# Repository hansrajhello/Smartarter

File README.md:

# Smartarter
This is an Arduino based project to automate the operation of Irrigation pumps.

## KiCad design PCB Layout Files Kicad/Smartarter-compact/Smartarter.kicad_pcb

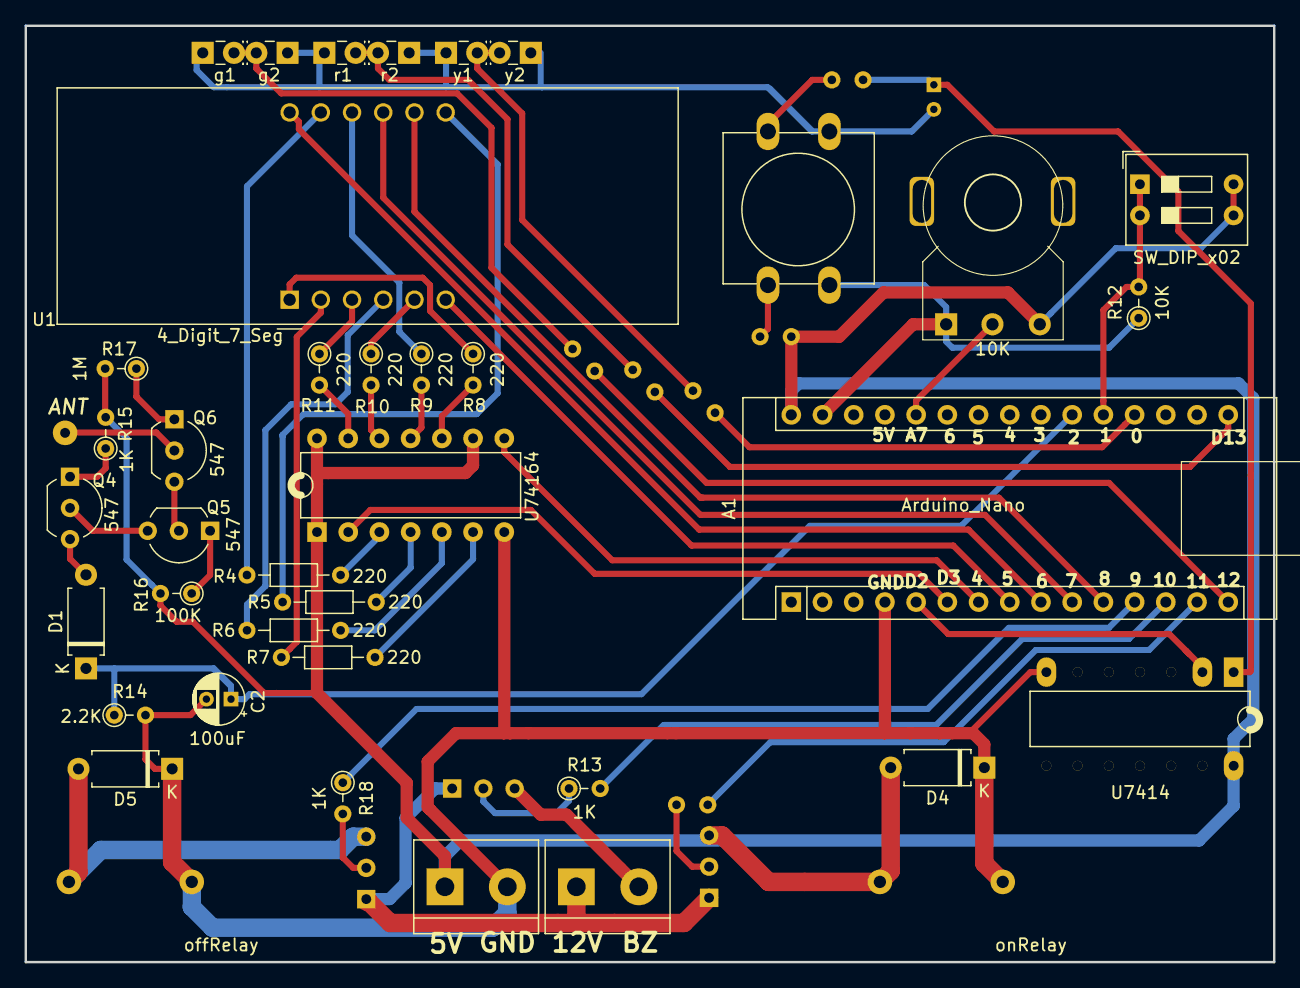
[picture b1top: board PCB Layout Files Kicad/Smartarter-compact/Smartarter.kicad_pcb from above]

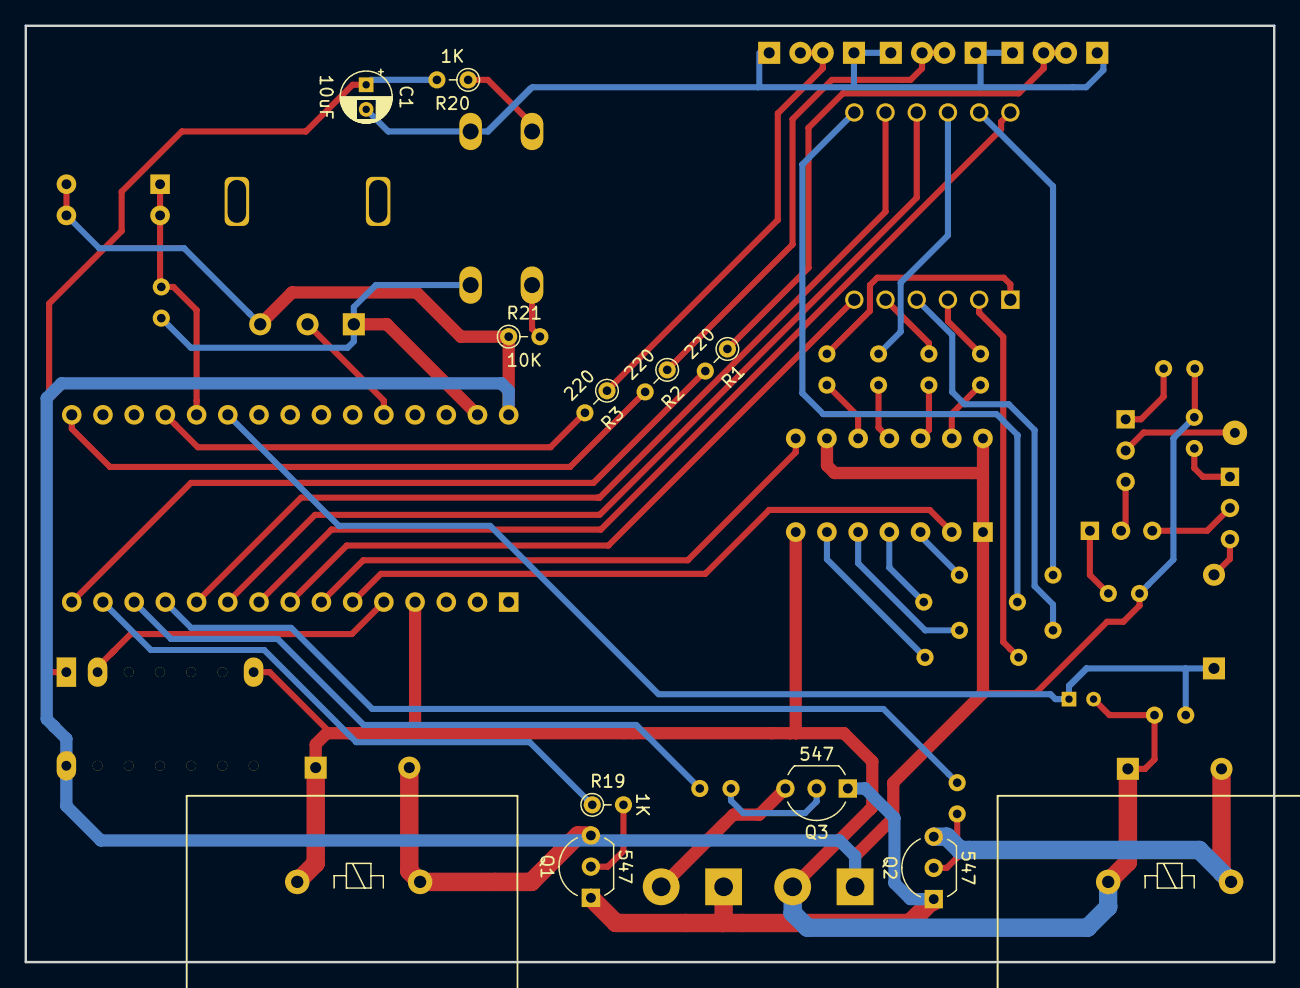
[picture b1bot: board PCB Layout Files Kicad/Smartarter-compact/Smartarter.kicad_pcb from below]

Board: 2 copper layers, 101.6 x 76.2 mm, 50 parts (12 on the bottom side), 53 nets.

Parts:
A1: Arduino_Nano
ANT1: ANT; SolderWirePad_1x01_Drill0.8mm
C1: 10uF; CP_Radial_D4.0mm_P2.00mm
C2: 100uF; CP_Radial_D4.0mm_P2.00mm
D1: D; D_A-405_P7.62mm_Horizontal
D4, D5: DIODE; D_A-405_P7.62mm_Horizontal
J1, J2: Screw_Terminal_01x02; TerminalBlock_bornier-2_P5.08mm
POT1: 10K; Potentiometer_Alpha_Round_P7.5
Q1, Q2, Q3, Q4, Q5, Q6: 547; TO-92_Inline_Wide
R1, R2, R3, R8, R9, R10, R11: 220; R_Axial_DIN0204_L3.6mm_D1.6mm_P2.54mm_Vertical
R4, R5, R6, R7: 220; R_Axial_DIN0204_L3.6mm_D1.6mm_P7.62mm_Horizontal
R12, R21: 10K; R_Axial_DIN0204_L3.6mm_D1.6mm_P2.54mm_Vertical
R13, R15, R18, R19, R20: 1K; R_Axial_DIN0204_L3.6mm_D1.6mm_P2.54mm_Vertical
R14: 2.2K; R_Axial_DIN0204_L3.6mm_D1.6mm_P2.54mm_Vertical
R16: 100K; R_Axial_DIN0204_L3.6mm_D1.6mm_P2.54mm_Vertical
R17: 1M; R_Axial_DIN0204_L3.6mm_D1.6mm_P2.54mm_Vertical
SW1: SW_Push; SW_PUSH-12mm
SW2: SW_DIP_x02; SW_DIP_SPSTx02_Slide_9.78x7.26mm_W7.62mm_P2.54mm
U1: 4_Digit_7_Seg; CA56-12EWA
U7414: 7414; DIP-14_W7.62mm_LongPads_Hansu
U74164: 74164; DIP-14_W7.62mm
g1, g2: onLED; LED_Rectangular_W3.9mm_H1.8mm
offRelay1: offRelay; Relay_SPDT_HUGE_32mm
onRelay1: onRelay; Relay_SPDT_HUGE_32mm
r1, r2: offLED; LED_Rectangular_W3.9mm_H1.8mm
y1, y2: otherLED; LED_Rectangular_W3.9mm_H1.8mm

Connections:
+5V: A1.30, J2.1, POT1.3, R15.2, R16.2, R17.2, R21.1, SW2.3, SW2.4, U7414.14, U74164.1, U74164.9, U74164.14
+12V: J1.1, Q1.1, Q2.1, Q3.1
/CLK: A1.7, U74164.8
/D1: A1.9, U1.12
/D2: A1.10, U1.9
/D3: A1.11, U1.8
/D4: A1.8, U1.6
/buzz: A1.13, R13.2
/bz: J1.2, Q3.3
/data: A1.6, U74164.2
/monitor: A1.21, C2.1, D1.1, R14.1
/offLed: A1.16, R2.2
/offRelay: A1.12, R18.1
/onLed: A1.15, R1.2
/onRelay: A1.14, R19.1
/otherLed: A1.19, R3.2
/pot: A1.26, POT1.2
/pushButton: A1.5, U7414.2
/slideSwitch: A1.20, R12.2, SW2.1, SW2.2
GND: A1.4, A1.29, C1.2, C2.2, D4.1, D5.1, J2.2, POT1.1, R12.1, R14.2, SW1.1, U7414.7, U74164.7, g1.1, g2.1, offRelay1.5, onRelay1.5, r1.1, r2.1, y1.1, y2.1
unnamed: ANT1.1, Q6.2
unnamed: C1.1, R20.2, U7414.1
unnamed: D1.2, Q4.3
unnamed: D4.2, Q1.3, onRelay1.1
unnamed: D5.2, Q2.3, offRelay1.1
unnamed: Q1.2, R19.2
unnamed: Q2.2, R18.2
unnamed: Q3.2, R13.1
unnamed: Q4.1, R15.1
unnamed: Q4.2, Q5.3
unnamed: Q5.1, R16.1
unnamed: Q5.2, Q6.3
unnamed: Q6.1, R17.1
unnamed: R1.1, g1.2, g2.2
unnamed: R2.1, r1.2, r2.2
unnamed: R3.1, y1.2, y2.2
unnamed: R4.1, U1.11
unnamed: R4.2, U74164.3
unnamed: R5.1, U1.7
unnamed: R5.2, U74164.4
unnamed: R6.1, U1.4
unnamed: R6.2, U74164.5
unnamed: R7.1, U1.2
unnamed: R7.2, U74164.6
unnamed: R8.1, U1.1
unnamed: R8.2, U74164.10
unnamed: R9.1, U1.10
unnamed: R9.2, U74164.11
unnamed: R10.1, U1.5
unnamed: R10.2, U74164.12
unnamed: R11.1, U1.3
unnamed: R11.2, U74164.13
unnamed: R20.1, R21.2, SW1.2

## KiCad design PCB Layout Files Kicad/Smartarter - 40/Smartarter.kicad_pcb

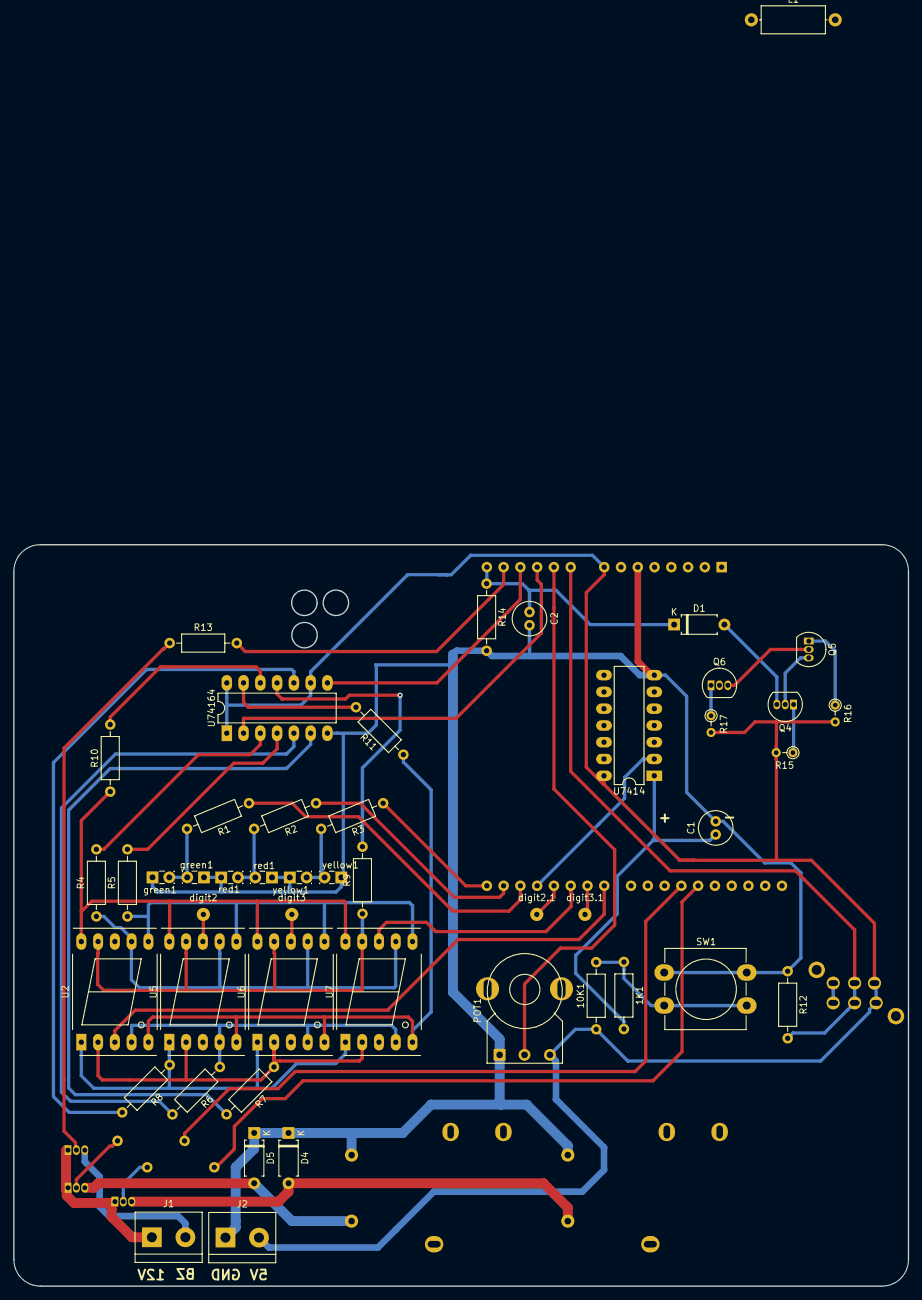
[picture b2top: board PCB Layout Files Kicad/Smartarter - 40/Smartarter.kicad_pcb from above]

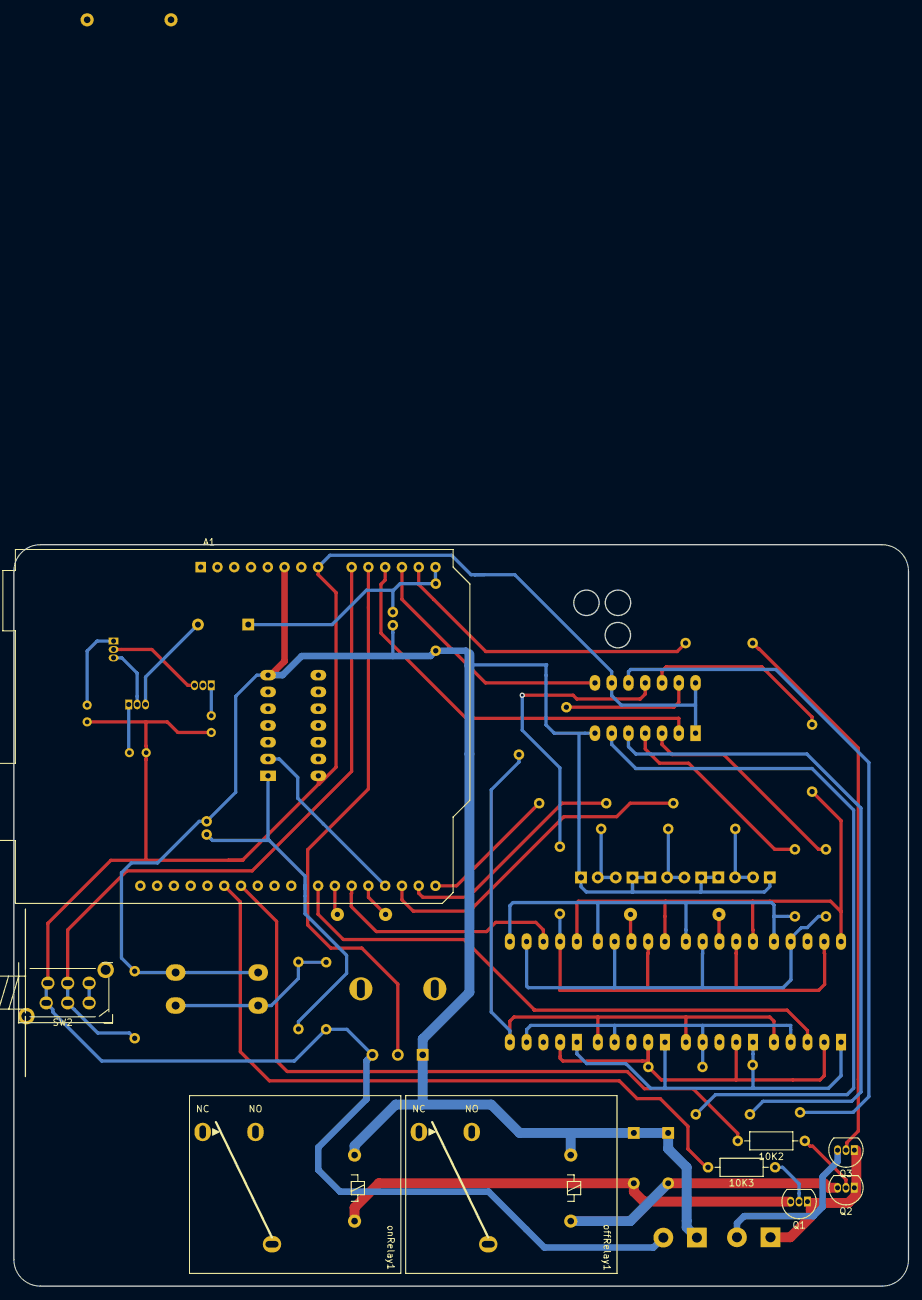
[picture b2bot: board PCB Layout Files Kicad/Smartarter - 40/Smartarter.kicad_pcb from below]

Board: 2 copper layers, 135.5 x 112.3 mm, 57 parts (9 on the bottom side), 54 nets.

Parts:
1K1, 10K1, 10K2, 10K3: R; R_Axial_DIN0207_L6.3mm_D2.5mm_P10.16mm_Horizontal
A1: Arduino_UNO_R3
C1, C2: C; C_Radial_D5.0mm_H11.0mm_P2.00mm
D1: D; D_A-405_P7.62mm_Horizontal
D4, D5: DIODE; D_A-405_P7.62mm_Horizontal
J1, J2: Screw_Terminal_01x02; TerminalBlock_bornier-2_P5.08mm
L1: INDUCTOR; L_Axial_L9.5mm_D4.0mm_P12.70mm_Horizontal_Fastron_SMCC
POT1: R_POT; Potentiometer_Alpha_Round_P7.5
Q1, Q2, Q3, Q4, Q5, Q6: BC547; TO-92_Inline
R1, R2, R3, R4, R5, R6, R7, R8, R9, R10, R11, R12, R13, R14: R; R_Axial_DIN0207_L6.3mm_D2.5mm_P10.16mm_Horizontal
R15, R16, R17: R; R_Axial_DIN0204_L3.6mm_D1.6mm_P2.54mm_Vertical
SW1: SW_Push; SW_PUSH-12mm_Wuerth-430476085716
SW2: SW_DPDT_x2; SW_6-Pin-Switch_Self_Lock_DPDT_Latching
U2, U5, U6, U7: KCSA02-107; 7SegmentLED_LTS6760_LTS6780
U7414: 7414; DIP-14_W7.62mm_LongPads
U74164: 74164; DIP-14_W7.62mm_LongPads
digit2, digit2.1, digit3, digit3.1: HEADER-1x01; SolderWirePad_1x01_Drill0.8mm
green1, green1#2: onLED; LED_Rectangular_W3.9mm_H1.8mm
offRelay1: offRelay; Relay_SPDT_HUGE_32mm
onRelay1: onRelay; Relay_SPDT_HUGE_32mm
red1, red1#2: offLED; LED_Rectangular_W3.9mm_H1.8mm
yellow1, yellow1#2: otherLED; LED_Rectangular_W3.9mm_H1.8mm

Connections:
+5V: 10K1.1, A1.8, J2.2, POT1.3, R15.2, R16.2, R17.2, SW2.3, SW2.6, U7414.14, U74164.1, U74164.9, U74164.14
+12V: J1.1, Q1.1, Q2.1, Q3.1
/A0: R4.1, U2.7, U5.7, U6.7, U7.7
/A1: R5.1, U2.6, U5.6, U6.6, U7.6
/A2: R6.1, U2.4, U5.4, U6.4, U7.4
/A3: R7.1, U2.2, U5.2, U6.2, U7.2
/A4: R8.1, U2.1, U5.1, U6.1, U7.1
/A5: R9.1, U2.9, U5.9, U6.9, U7.9
/A6: R10.1, U2.10, U5.10, U6.10, U7.10
/A7: R11.1, U2.5, U5.5, U6.5, U7.5
/CLK: A1.12, U74164.8
/D1: A1.22, U2.3
/D4: A1.20, U7.8
/buzz: A1.13, R13.2
/data: A1.11, U74164.2
/monitor: A1.14, C2.1, D1.1, R14.1
/offLed: A1.16, R2.1
/onLed: A1.17, R1.1
/otherLed: A1.15, R3.1
/pot: A1.10, POT1.2
/pushButton: A1.18, U7414.2
/slideSwitch: A1.9, R12.2, SW2.2, SW2.5
GND: A1.6, C1.2, C2.2, D4.1, D5.1, J2.1, POT1.1, R12.1, R14.2, SW1.1, U7414.7, U74164.7, green1.1, green1#2.1, offRelay1.5, onRelay1.5, red1.1, red1#2.1, yellow1.1, yellow1#2.1
unnamed: 1K1.2, C1.1, U7414.1
unnamed: 1K1.1, 10K1.2, SW1.2
unnamed: 10K2.1, Q2.2
unnamed: 10K3.1, Q1.2
unnamed: A1.19, digit2.1.1
unnamed: A1.21, digit3.1.1
unnamed: D1.2, Q4.3
unnamed: D4.2, Q1.3, onRelay1.1
unnamed: D5.2, Q2.3, offRelay1.1
unnamed: J1.2, Q3.3
unnamed: L1.1, Q6.2
unnamed: Q3.2, R13.1
unnamed: Q4.1, R15.1
unnamed: Q4.2, Q5.3
unnamed: Q5.1, R16.1
unnamed: Q5.2, Q6.3
unnamed: Q6.1, R17.1
unnamed: R1.2, green1.2, green1#2.2
unnamed: R2.2, red1.2, red1#2.2
unnamed: R3.2, yellow1.2, yellow1#2.2
unnamed: R4.2, U74164.3
unnamed: R5.2, U74164.4
unnamed: R6.2, U74164.5
unnamed: R7.2, U74164.6
unnamed: R8.2, U74164.10
unnamed: R9.2, U74164.11
unnamed: R10.2, U74164.12
unnamed: R11.2, U74164.13
unnamed: SW2.1, SW2.4
unnamed: U5.8, digit2.1
unnamed: U6.8, digit3.1

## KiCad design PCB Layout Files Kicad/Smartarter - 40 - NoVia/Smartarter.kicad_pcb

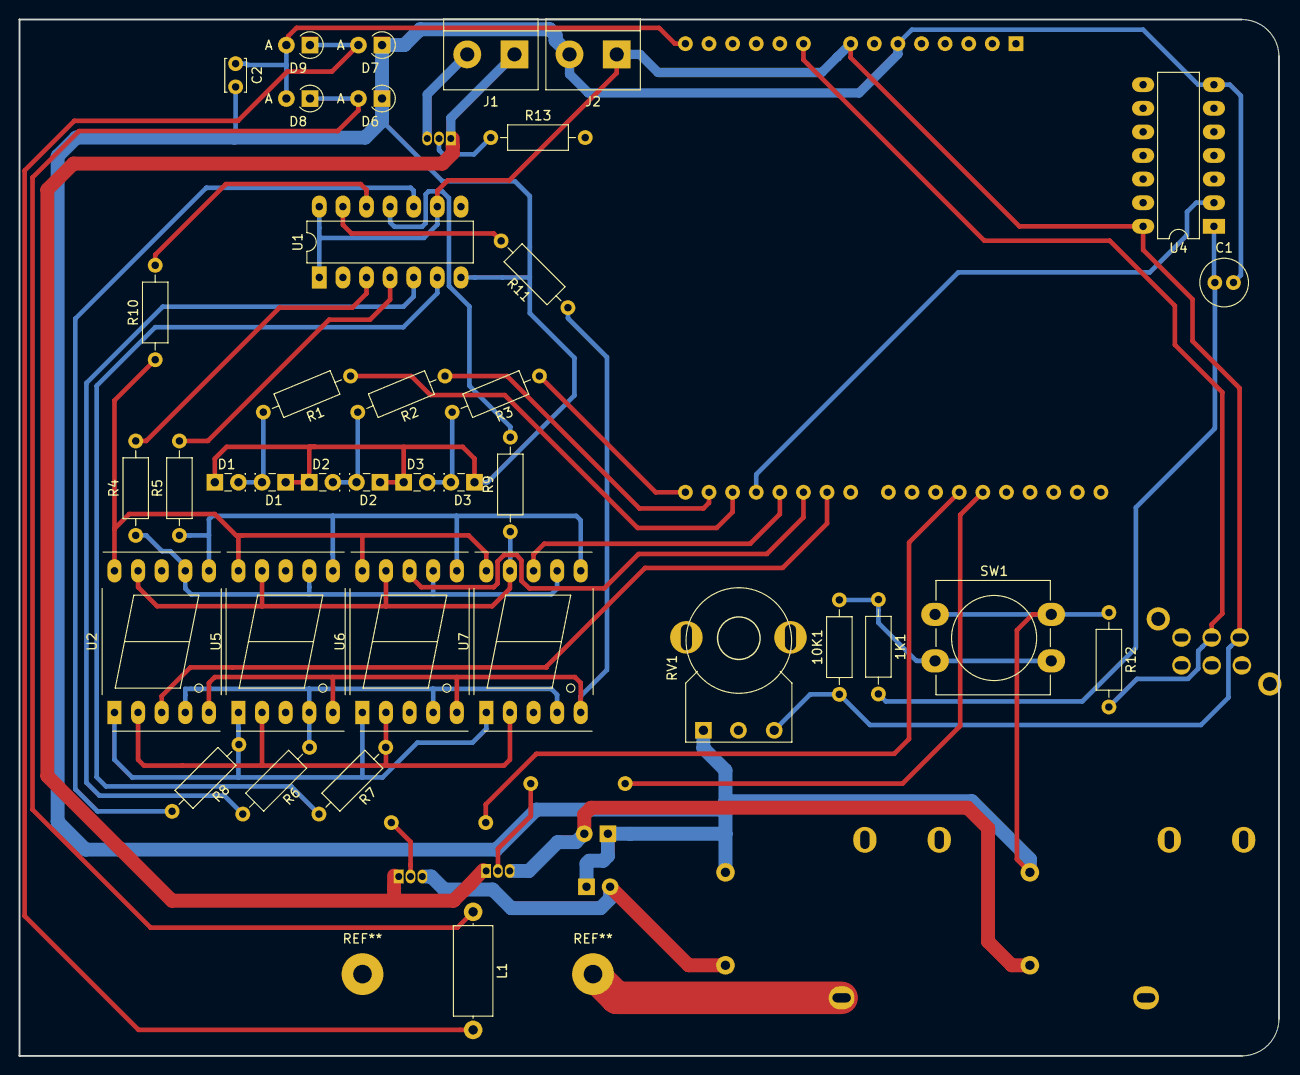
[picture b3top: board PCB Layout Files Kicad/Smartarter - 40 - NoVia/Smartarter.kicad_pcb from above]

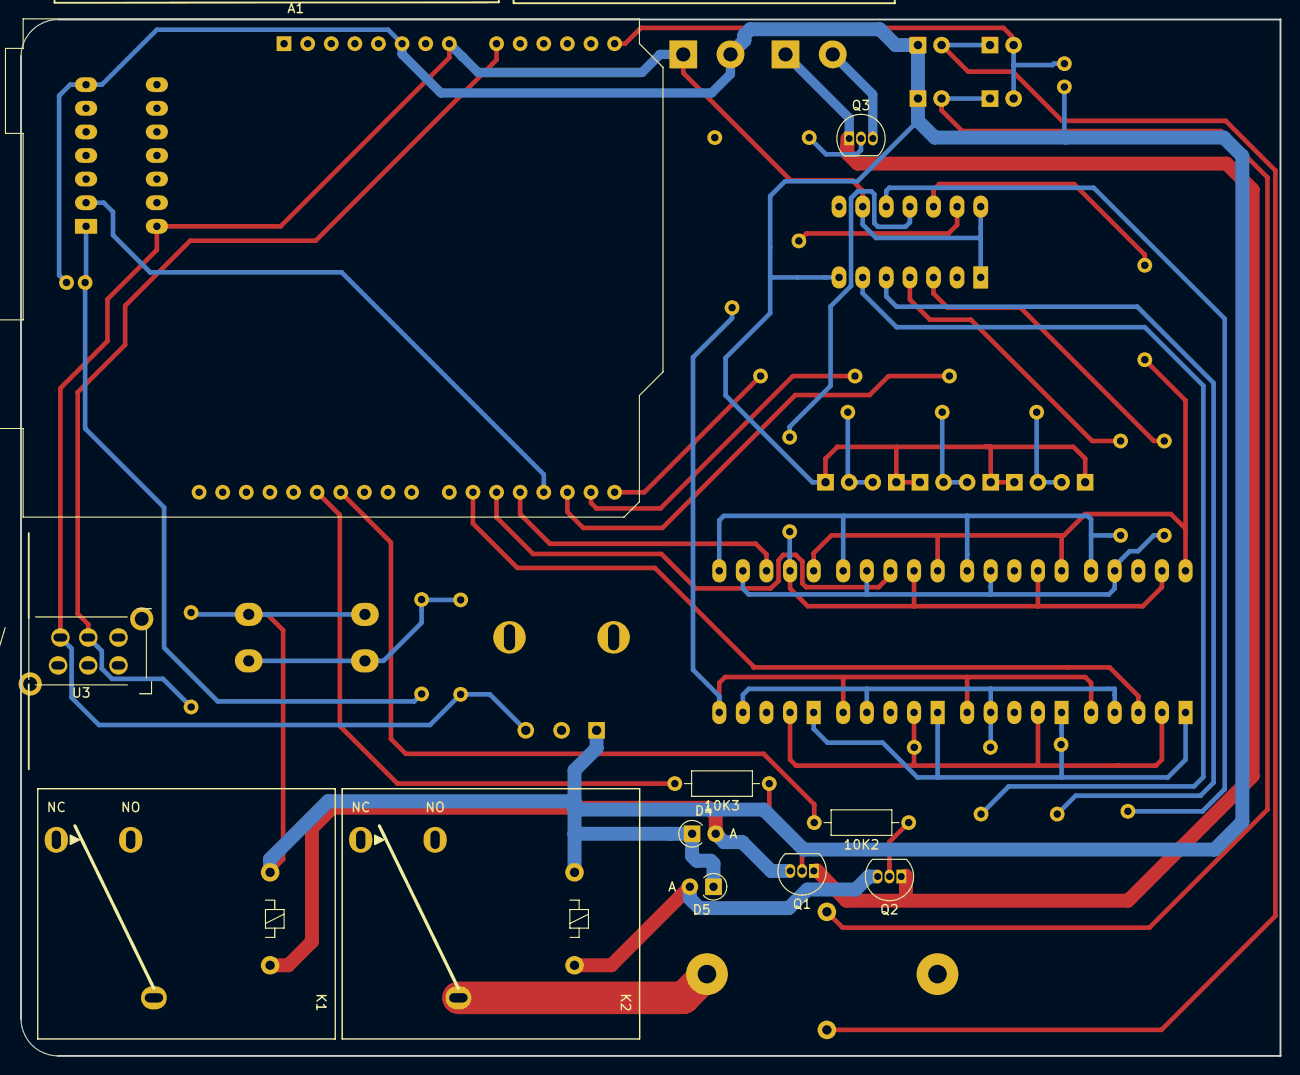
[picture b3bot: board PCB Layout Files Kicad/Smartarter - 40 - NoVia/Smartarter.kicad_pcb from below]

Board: 2 copper layers, 135.5 x 111.5 mm, 49 parts (11 on the bottom side), 35 nets.

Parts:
1K1, 10K1, 10K2, 10K3: R; R_Axial_DIN0207_L6.3mm_D2.5mm_P10.16mm_Horizontal
A1: Arduino_UNO_R3
C1: C; C_Radial_D5.0mm_H11.0mm_P2.00mm
C2: C_Small; C_Disc_D3.4mm_W2.1mm_P2.50mm
D1, D1#2: onLED; LED_Rectangular_W3.9mm_H1.8mm
D2, D2#2: offLED; LED_Rectangular_W3.9mm_H1.8mm
D3, D3#2: otherLED; LED_Rectangular_W3.9mm_H1.8mm
D4, D5, D6, D7, D8, D9: DIODE; D_A-405_P2.54mm_Vertical_AnodeUp
J1, J2: Screw_Terminal_01x02; TerminalBlock_bornier-2_P5.08mm
K1: onRelay; Relay_SPDT_HUGE_32mm
K2: offRelay; Relay_SPDT_HUGE_32mm
L1: INDUCTOR; L_Axial_L9.5mm_D4.0mm_P12.70mm_Horizontal_Fastron_SMCC
Q1, Q2, Q3: BC547; TO-92_Inline
R1, R2, R3, R4, R5, R6, R7, R8, R9, R10, R11, R12, R13: R; R_Axial_DIN0207_L6.3mm_D2.5mm_P10.16mm_Horizontal
RV1: R_POT; Potentiometer_Alpha_Round_P7.5
SW1: SW_Push; SW_PUSH-12mm_Wuerth-430476085716
U1: 74164; DIP-14_W7.62mm_LongPads
U2, U5, U6, U7: KCSA02-107; 7SegmentLED_LTS6760_LTS6780
U3: slideSwitch; SW_6-Pin-Switch_Self_Lock_DPDT_Latching
U4: 7414; DIP-14_W7.62mm_LongPads

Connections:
+5V: 10K1.1, A1.8, J2.1, RV1.3, U1.1, U1.9, U1.14, U3.6, U4.14
+12V: J1.1, Q1.1, Q2.1, Q3.1
/A0: R4.1, U2.7, U5.7, U6.7, U7.7
/A1: R5.1, U2.6, U5.6, U6.6, U7.6
/A2: R6.1, U2.4, U5.4, U6.4, U7.4
/A3: R7.1, U2.2, U5.2, U6.2, U7.2
/A4: R8.1, U2.1, U5.1, U6.1, U7.1
/A5: R9.1, U2.9, U5.9, U6.9, U7.9
/A6: R10.1, U2.10, U5.10, U6.10, U7.10
/A7: R11.1, U2.5, U5.5, U6.5, U7.5
GND: A1.6, C1.2, C2.2, D1.1, D1#2.1, D2.1, D2#2.1, D3.1, D3#2.1, D4.1, D5.1, D6.1, D7.1, J2.2, K1.5, K2.5, R12.1, RV1.1, SW1.1, U1.7, U4.7
unnamed: 1K1.2, C1.1, U4.1
unnamed: 1K1.1, 10K1.2, SW1.2
unnamed: 10K2.1, Q2.2
unnamed: 10K3.1, Q1.2
unnamed: A1.9, R12.2, U3.5
unnamed: A1.14, C2.1, D8.2, D9.2
unnamed: A1.18, U4.2
unnamed: D1.2, D1#2.2, R1.2
unnamed: D2.2, D2#2.2, R2.2
unnamed: D3.2, D3#2.2, R3.2
unnamed: D4.2, K1.1, Q1.3
unnamed: D5.2, K2.1, Q2.3
unnamed: D6.2, D8.1, L1.1
unnamed: D7.2, D9.1, L1.2
unnamed: J1.2, Q3.3
unnamed: Q3.2, R13.1
unnamed: R4.2, U1.3
unnamed: R5.2, U1.4
unnamed: R6.2, U1.5
unnamed: R7.2, U1.6
unnamed: R8.2, U1.10
unnamed: R9.2, U1.11
unnamed: R10.2, U1.12
unnamed: R11.2, U1.13

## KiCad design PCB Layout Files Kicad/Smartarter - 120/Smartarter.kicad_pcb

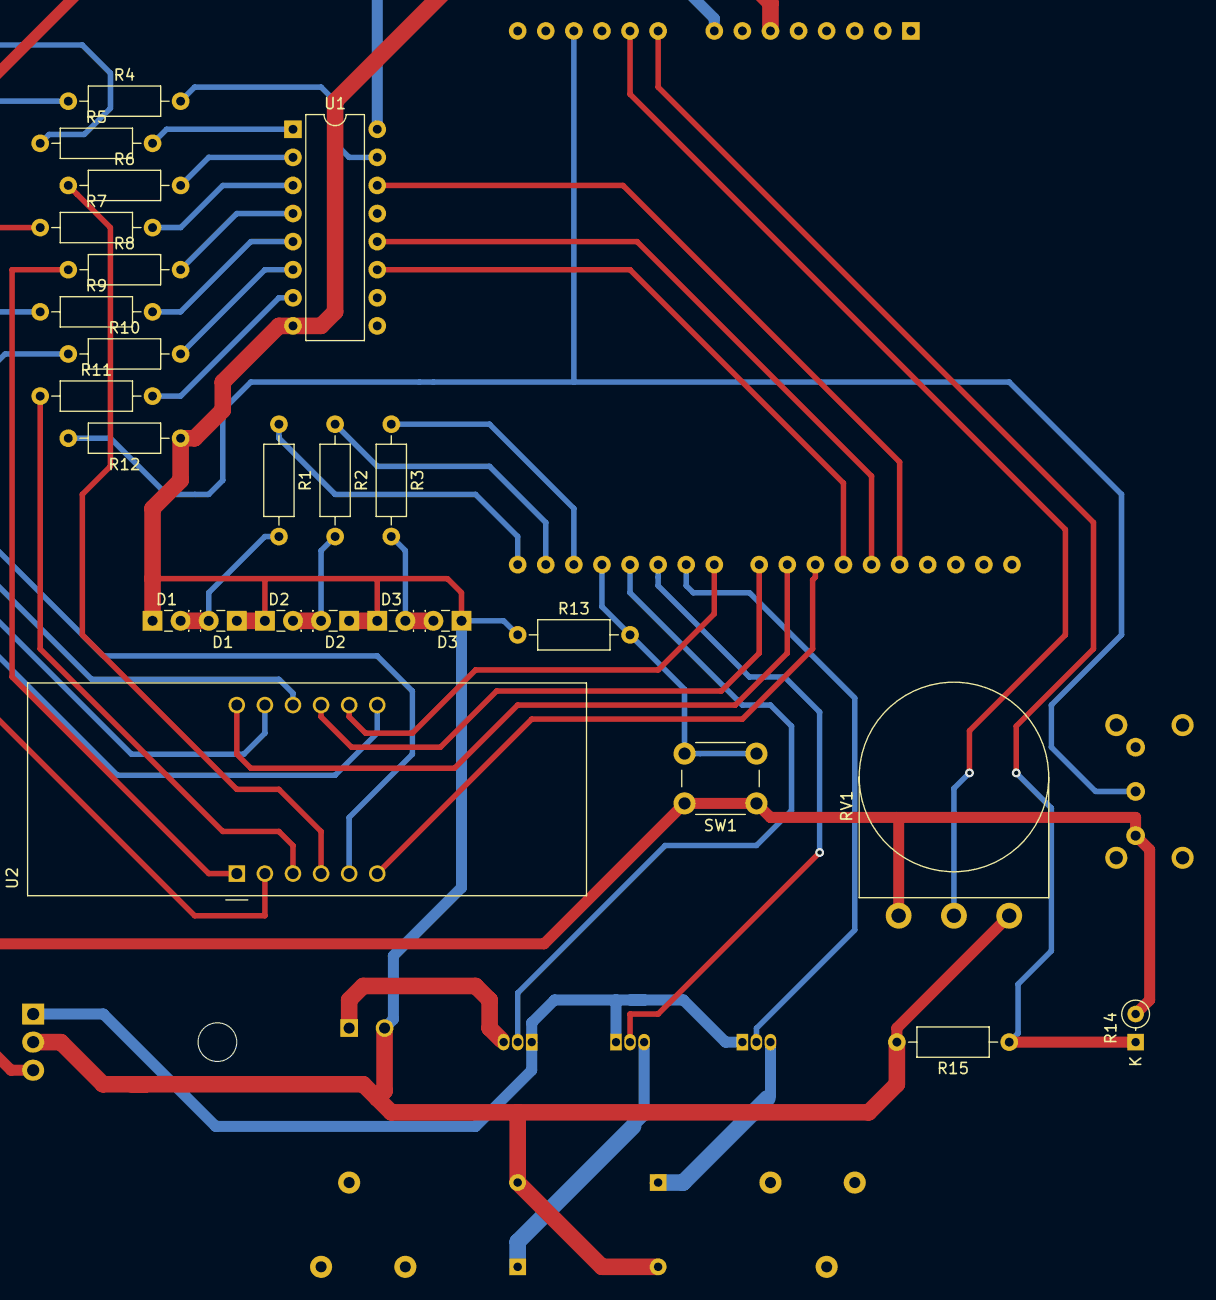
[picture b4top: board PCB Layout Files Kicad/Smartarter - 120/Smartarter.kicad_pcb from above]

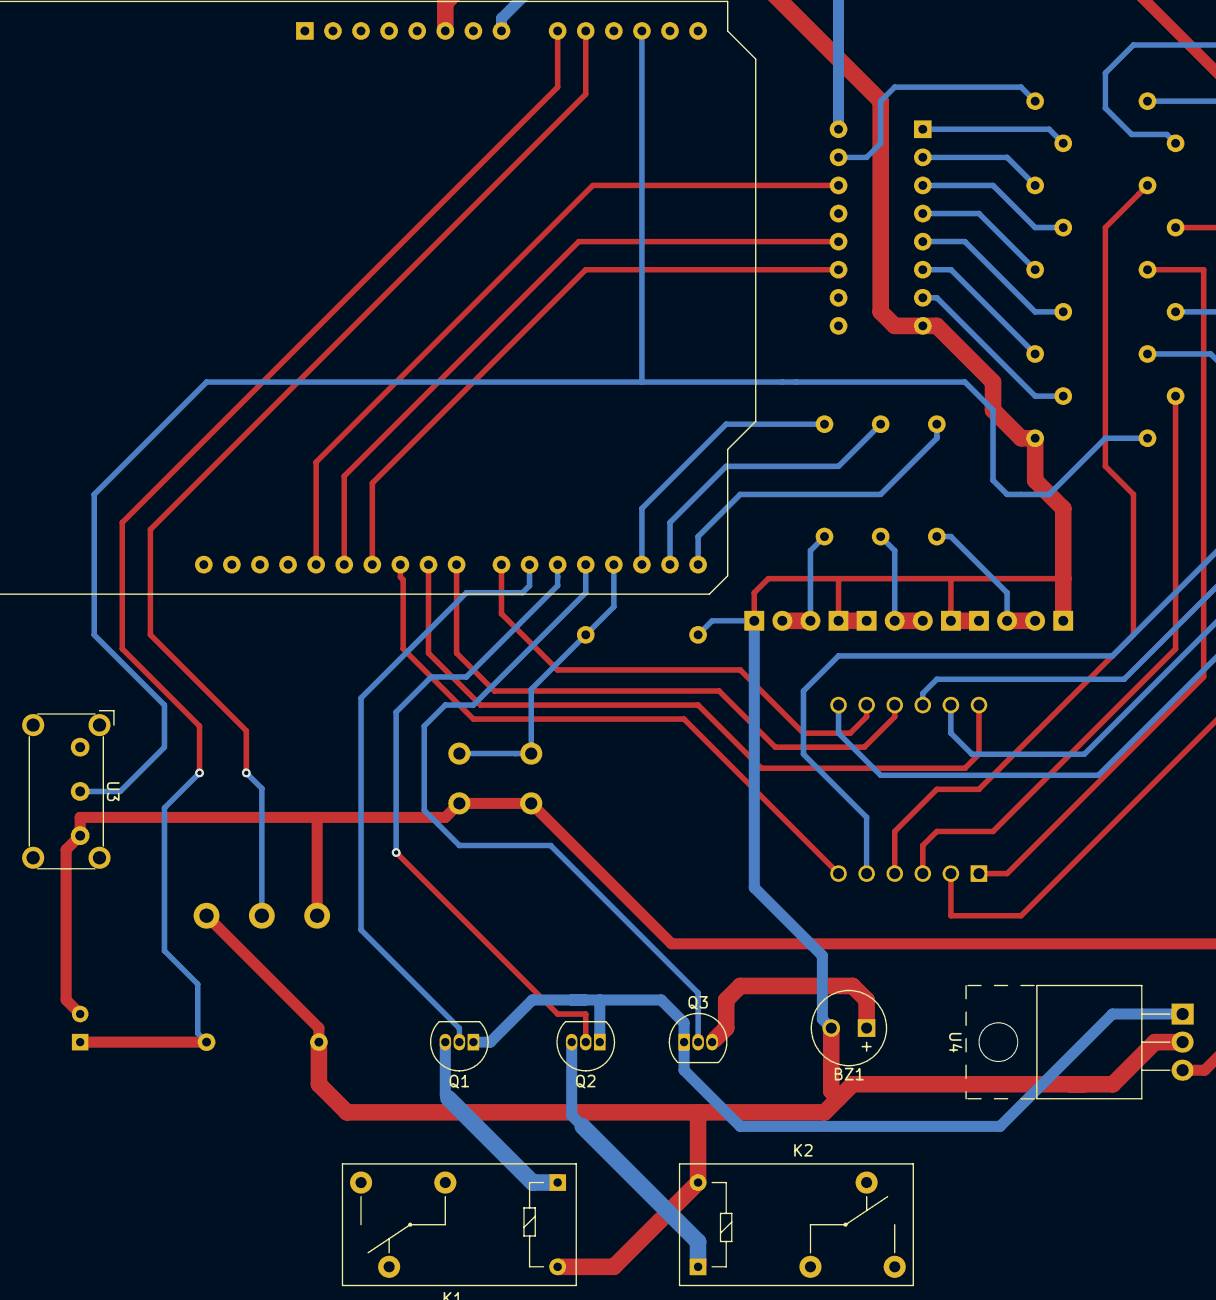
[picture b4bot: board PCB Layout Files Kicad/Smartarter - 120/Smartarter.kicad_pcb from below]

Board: 2 copper layers, 34 parts (9 on the bottom side), 42 nets.

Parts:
A1: Arduino_UNO_R3
BZ1: Buzzer; MagneticBuzzer_Kingstate_KCG0601
D1, D1#2: onLED; LED_Rectangular_W3.9mm_H1.8mm
D2, D2#2: offLED; LED_Rectangular_W3.9mm_H1.8mm
D3, D3#2: otherLED; LED_Rectangular_W3.9mm_H1.8mm
K1: onRelay; Relay_SPDT_Omron-G5Q-1
K2: offRelay; Relay_SPDT_Omron-G5Q-1
Q1, Q2, Q3: BC547; TO-92_Inline
R1, R2, R3, R4, R5, R6, R7, R8, R9, R10, R11, R12, R13, R15: R; R_Axial_DIN0207_L6.3mm_D2.5mm_P10.16mm_Horizontal
R14: R_PHOTO; D_DO-34_SOD68_P2.54mm_Vertical_KathodeUp
RV1: R_POT; Potentiometer_Omeg_PC16BU_Vertical
SW1: SW_Push; SW_PUSH_6mm_H13mm
U1: 74HC595; DIP-16_W7.62mm
U2: 7-seg; CA56-12EWA
U3: slideSwitch; SW_E-Switch_EG1224_SPDT_Angled
U4: L7805; TO-220-3_Horizontal_TabUp

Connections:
+12V: Q1.1, Q2.1, Q3.1, U4.1
GND: A1.6, BZ1.2, D1.1, D1#2.1, D2.1, D2#2.1, D3.1, D3#2.1, K1.5, K2.5, R12.1, R13.1, R15.2, RV1.1, U1.8, U4.2
unnamed: A1.8, R14.2, RV1.3, SW1.1, U1.16, U3.3, U4.3
unnamed: A1.9, R14.1, R15.1
unnamed: A1.10, RV1.2
unnamed: A1.12, R12.2, U3.2
unnamed: A1.15, R1.1
unnamed: A1.16, R2.1
unnamed: A1.17, R3.1
unnamed: A1.18, R13.2, SW1.2
unnamed: A1.19, Q3.2
unnamed: A1.20, Q2.2
unnamed: A1.21, Q1.2
unnamed: A1.22, U2.8
unnamed: A1.23, U2.9
unnamed: A1.24, U2.12
unnamed: A1.25, U2.6
unnamed: A1.26, U1.11
unnamed: A1.27, U1.12
unnamed: A1.28, U1.14
unnamed: BZ1.1, Q3.3
unnamed: D1.2, D1#2.2, R1.2
unnamed: D2.2, D2#2.2, R2.2
unnamed: D3.2, D3#2.2, R3.2
unnamed: K1.1, Q1.3
unnamed: K2.1, Q2.3
unnamed: R4.1, U2.11
unnamed: R4.2, U1.15
unnamed: R5.1, U2.7
unnamed: R5.2, U1.1
unnamed: R6.1, U2.4
unnamed: R6.2, U1.2
unnamed: R7.1, U2.2
unnamed: R7.2, U1.3
unnamed: R8.1, U2.1
unnamed: R8.2, U1.4
unnamed: R9.1, U2.10
unnamed: R9.2, U1.5
unnamed: R10.1, U2.5
unnamed: R10.2, U1.6
unnamed: R11.1, U2.3
unnamed: R11.2, U1.7

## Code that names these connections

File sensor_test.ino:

#define clockPin 4
#define dataPin 3
#define digitOne 6
#define digitTwo 7
#define digitThree 8
#define digitFour 5
#define onLed 12
#define offLed 13
#define otherLed A0

#define onRelay 11
#define offRelay 9
#define buzzer 10


#define slideSwitch A1
#define pot A7
#define pushButton 2
#define monitorPin A2

const byte digit_pattern[16] =
{
  B00111111,  // 0
  B00000110,  // 1
  B01011011,  // 2
  B01001111,  // 3
  B01100110,  // 4
  B01101101,  // 5
  B01111101,  // 6
  B00000111,  // 7
  B01111111,  // 8
  B01101111,  // 9
  B01110111,  // A
  B01111100,  // b
  B00111001,  // C
  B01011110,  // d
  B01111001,  // E
  B01110001   // F
};     


void setup() {
  Serial.begin(9600);
  
  pinMode(clockPin, OUTPUT);
  pinMode(dataPin, OUTPUT);
  pinMode(digitOne, OUTPUT);
  pinMode(digitTwo, OUTPUT);
  pinMode(digitThree, OUTPUT);
  pinMode(onLed, OUTPUT);
  pinMode(offLed, OUTPUT);
  pinMode(otherLed, OUTPUT);
  
  pinMode(slideSwitch, INPUT);
  pinMode(pot, INPUT);
  pinMode(monitorPin, INPUT);
  pinMode(pushButton, INPUT_PULLUP);
  
  byte outputBits = B01111111;
  deActivate();
  shiftOut(dataPin, clockPin, MSBFIRST, ~outputBits);  // shiftOut takes the byte, performs SIPO on the shift register
  digitalWrite(digitThree, HIGH);
}

void loop() {
  for (int i=0; i<10; i++)
  {
    byte outputBits = digit_pattern[i];
    deActivate();
    shiftOut(dataPin, clockPin, MSBFIRST, ~outputBits);  // shiftOut takes the byte, performs SIPO on the shift register
    digitalWrite(digitOne, HIGH);
    delay(500);
    digitalWrite(digitOne, LOW);
    digitalWrite(digitTwo, HIGH);
    delay(500);
    digitalWrite(digitTwo, LOW);
    digitalWrite(digitThree, HIGH);
    delay(500);
    digitalWrite(digitThree, LOW);
    digitalWrite(digitFour, HIGH);
    delay(500);
    digitalWrite(digitFour, LOW);
  }
}

void deActivate(){
  digitalWrite(digitOne, LOW);
  digitalWrite(digitTwo, LOW);
  digitalWrite(digitThree, LOW);
}

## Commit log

2019-08-21 only pot and seven segment working great.\nThe pushButton and unintended save not implemented
2019-08-21 PushButton Working Fine, Just fixed unwanted saving
2019-08-21 Unwanted Saving also solved
2019-08-21 After Fine tuning, the Editing Code is perfectly ready.
2019-09-26 NotEditing code added
2019-09-26 PCB Layout files added
2019-09-26 PCB Screenshots added
2019-09-27 Simulation code perfect but 74595 used. Modify for 74164
2019-09-27 Breadboard code perfectly working, resolve power issues
2019-09-29 40 seven seg PCB updated
2019-10-01 inductor and full wave rectifier implemented in both schematic and layout
2019-10-01 chaar bilang chhota kar diya
2019-10-01 40 without via done (arduino IO remaining); TODO: work in 40 now
2019-10-02 all tracks set in 40; double check the connections and HOLA ;)
2019-10-10 Almost done
2019-10-10 PCB Layout perfectly done
2019-10-10 Snapshots updated
2019-10-12 PCB Layout for 4x3'' addedgit status
2019-10-13 Ready for Ahmedabad
2019-11-21 Finalized compact pcb layout
2019-12-27 online backup, pcb display code and TODO some changes to be done in PCB
2020-01-04 Merged code updated; bypassed sensorpin
2021-03-20 The most optimized code
